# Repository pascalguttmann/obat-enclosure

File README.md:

# Obat - Enclosure

KiCAD Project for the Enclosure adapter PCB to interface to the mechanical Enclosure.

| TOP | BOT |
| ------------- | -------------- |
|  |  |
|  |  |

## License

This repository is licensed under the MIT license.

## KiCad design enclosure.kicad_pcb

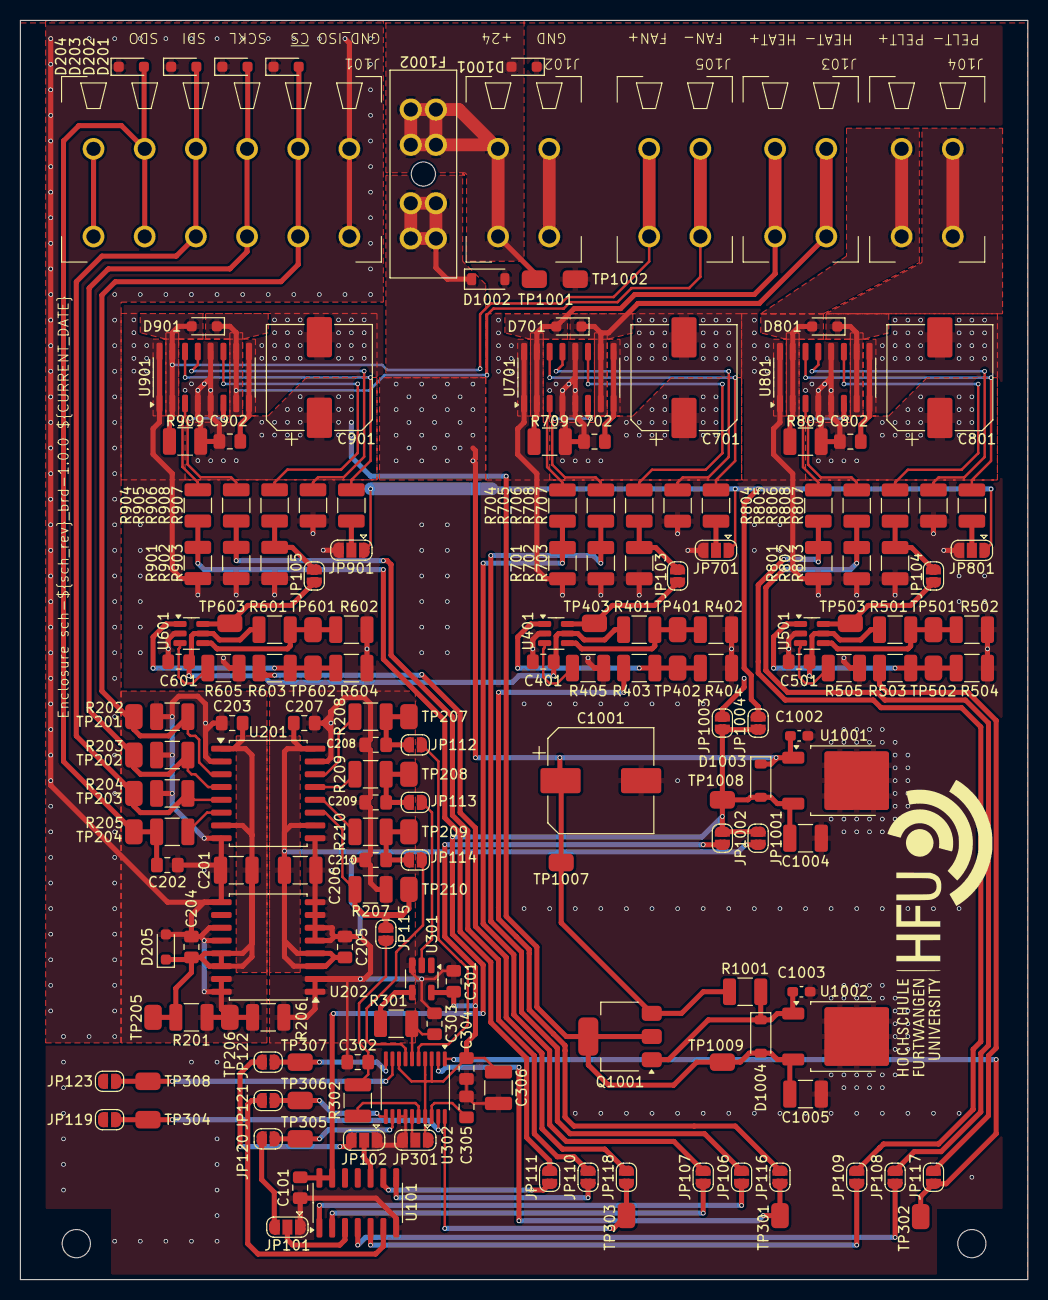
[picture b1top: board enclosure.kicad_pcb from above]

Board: 2 copper layers, 100.0 x 125.0 mm, 181 parts (0 on the bottom side), 100 nets.

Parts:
C101, C203, C204, C205, C207, C301, C304, C305, C401, C501, C601, C702, C802, C902: 100n; C_0805_2012Metric_Pad1.18x1.45mm_HandSolder
C201, C206, C306, C1004, C1005: 10u; C_1210_3225Metric_Pad1.33x2.70mm_HandSolder
C202, C208, C209, C210, C302, C303: 470p; C_0805_2012Metric_Pad1.18x1.45mm_HandSolder
C701, C801, C901, C1001: 470u; CP_Elec_10x10
C1002, C1003: 1u; C_0603_1608Metric_Pad1.08x0.95mm_HandSolder
D201, D202, D203, D204, D701, D801, D901, D1001: D_TVS; D_SOD-323_HandSoldering
D205: PDZ5.6B115; D_SOD-323_HandSoldering
D1002, D1003, D1004: 1N4148; D_SOD-123
F1002: Fuse_Socket; FuseHolder_Blade_ATO_Littelfuse_FLR_178.6165
J101: Conn_01x06_Socket; PhoenixContact_TDPT_2,5_6-SP-5,08_1x06_P5.08mm_Horizontal
J102, J103, J104, J105: Conn_01x02_Socket; PhoenixContact_TDPT_2,5_2-SP-5,08_1x02_P5.08mm_Horizontal
JP101, JP102, JP301, JP701, JP801, JP901: SolderJumper_3_Bridged12; SolderJumper-3_P1.3mm_Bridged12-Soldermask-Paste_RoundedPad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
JP103, JP104, JP105, JP106, JP107, JP108, JP109, JP110, JP111, JP112, JP113, JP114, JP115, JP116, JP117, JP118, JP119, JP120, JP121, JP122, JP123, JP1001, JP1002, JP1003, JP1004: SolderJumper_2_Open; SolderJumper-2_P1.3mm_Open_RoundedPad1.0x1.5mm
Q1001: DPLS350E; SOT-223-3_TabPin2
R201: 330; R_1210_3225Metric_Pad1.30x2.65mm_HandSolder
R202, R203, R204, R206, R207, R401, R501, R601, R701, R702, R703, R801, R802, R803, R901, R902, R903: 1M; R_1210_3225Metric_Pad1.30x2.65mm_HandSolder
R205, R208, R209, R210, R301, R302: 100; R_1210_3225Metric_Pad1.30x2.65mm_HandSolder
R402, R502, R602: 280k; R_1210_3225Metric_Pad1.30x2.65mm_HandSolder
R403, R503, R603, R709, R809, R909: 10k; R_1210_3225Metric_Pad1.30x2.65mm_HandSolder
R404, R504, R604: 2k49; R_1210_3225Metric_Pad1.30x2.65mm_HandSolder
R405, R505, R605: 100k; R_1210_3225Metric_Pad1.30x2.65mm_HandSolder
R704, R705, R706, R707, R708, R804, R805, R806, R807, R808, R904, R905, R906, R907, R908: 1k; R_1210_3225Metric_Pad1.30x2.65mm_HandSolder
R1001: 5R9; R_1210_3225Metric_Pad1.30x2.65mm_HandSolder
TP201, TP202, TP203, TP204, TP205, TP206, TP207, TP208, TP209, TP210, TP301, TP302, TP303, TP304, TP305, TP306, TP307, TP308, TP401, TP402, TP403, TP501, TP502, TP503, TP601, TP602, TP603, TP1001, TP1002, TP1007, TP1008, TP1009: TP_0805_2012Metric
U101: 4041; SOIC-14_3.9x8.7mm_P1.27mm
U201: Si8641BD-B-IS2; SOIC-16W_7.5x10.3mm_P1.27mm
U202: R05C05TE05S; SOIC-16W_7.5x10.3mm_P1.27mm
U301: SN74LVC1G04DBVR; SOT-23-5_HandSoldering
U302: AD567xR; TSSOP-20_4.4x6.5mm_P0.65mm
U401, U501, U601: LTC6992IS6-1; TSOT-23-6
U701, U801, U901: VNH7070ASTR; SO-16_3.9x9.9mm_P1.27mm
U1001: MC7805; TO-252-2
U1002: MC7812; TO-252-2

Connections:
+5VA: C101.2, C1004.2, D1003.2 (A), JP1001.1 (A), JP1002.1 (A), JP1003.1 (A), JP1004.1 (A), TP1008.1, U101.13, U101.14 (Vdd), U1001.3 (OUT)
+5VA_dac: C301.2, C304.2, C306.2, JP301.1 (A), JP1002.2 (B), U301.5 (VCC), U302.3 (VDD), U302.4 (VLOGIC), U302.8 (GAIN), U302.17 (~RESET)
+5VA_digital-interface: C205.2, C206.2, C207.2, JP1001.2 (B), U201.10 (EN2), U201.16 (VDD2), U202.3 (+VIN), U202.4 (+VIN)
+5VA_full-bridge: JP701.1 (A), JP801.1 (A), JP901.1 (A), JP1004.2 (B)
+5VA_pwm: C401.2, C501.2, C601.2, JP1003.2 (B), R401.2, R501.2, R601.2, U401.5 (V+), U501.5 (V+), U601.5 (V+)
+5VI: C201.2, C203.2, C204.2, D205.1 (K), R201.2, TP205.1, U201.1 (VDD1), U201.7 (EN1), U202.13 (+VOUT), U202.14 (+VOUT)
+12VA: C901.1, C902.2, C1005.2, D1004.2 (A), Q1001.2 (C), R909.2, TP1009.1, U901.4 (VCC), U901.5 (VCC), U901.12 (VCC), U1002.3 (OUT)
+24V: C701.1, C702.2, C801.1, C802.2, C1001.1, C1002.2, D1002.1 (K), D1003.1 (K), F1002.1, Q1001.3 (E), R709.2, R809.2, R1001.1, TP1007.1, U701.4 (VCC), U701.5 (VCC), U701.12 (VCC), U801.4 (VCC), U801.5 (VCC), U801.12 (VCC), U1001.1 (IN)
/SCKL: JP113.2 (B), U301.2 (A)
/SDI: JP114.2 (B), U302.7 (SDI)
/SDO: C302.2, JP115.2 (B), R302.1
/dac/dac_ch_0: JP116.1 (A), TP301.1, U302.2 (VOUT0)
/dac/dac_ch_1: JP117.1 (A), TP302.1, U302.1 (VOUT1)
/dac/dac_ch_2: JP118.1 (A), TP303.1, U302.20 (VOUT2)
/dac/dac_ch_3: JP119.1 (A), TP304.1, U302.19 (VOUT3)
/dac/dac_ch_4: JP120.1 (A), TP305.1, U302.12 (VOUT4)
/dac/dac_ch_5: JP121.1 (A), TP306.1, U302.11 (VOUT5)
/dac/dac_ch_6: JP122.1 (A), TP307.1, U302.10 (VOUT6)
/dac/dac_ch_7: JP123.1 (A), TP308.1, U302.9 (VOUT7)
/dac/~sckl: C303.2, R301.2, U302.6 (SCLK)
/dac_ch_0: JP116.2 (B), R403.2
/dac_ch_1: JP117.2 (B), R503.2
/dac_ch_2: JP118.2 (B), R603.2
/dac_ch_4: JP101.3 (B), JP120.2 (B)
/dac_ch_5: JP121.2 (B), U101.6
/dac_ch_6: JP102.3 (B), JP122.2 (B)
/digital-interface/SCKL: C209.2, JP113.1 (A), R209.2, TP208.1
/digital-interface/SCKL_ISO: D202.2 (A2), J101.3, R203.2, TP202.1, U201.4 (A2)
/digital-interface/SDI: C210.2, JP114.1 (A), R210.2, TP209.1
/digital-interface/SDI_ISO: D203.2 (A2), J101.4, R204.2, TP203.1, U201.5 (A3)
/digital-interface/SDO: JP115.1 (A), R207.2, TP210.1, U201.11 (B4)
/digital-interface/SDO_ISO: C202.2, D204.2 (A2), J101.5, R205.1, TP204.1
/digital-interface/sckl_pin: R209.1, U201.13 (B2)
/digital-interface/sdi_pin: R210.1, U201.12 (B3)
/digital-interface/sdo_iso_pin: R205.2, U201.6 (A4)
/digital-interface/~CS_ISO: D201.2 (A2), J101.2, R202.2, TP201.1, U201.3 (A1)
/digital-interface/~CS: C208.2, JP112.1 (A), R208.2, TP207.1
/digital-interface/~cs_pin: R208.1, U201.14 (B1)
/fan_+: D901.2 (A2), J105.2, R909.1, U901.2 (OUT_A), U901.15 (OUT_A)
/fan_-: D901.1 (A1), J105.1, U901.7 (OUT_B), U901.10 (OUT_B)
/full-bridge1/IN_A: JP109.2 (B), R801.2, R804.1
/full-bridge1/IN_B: JP108.2 (B), R802.2, R805.1
/full-bridge1/cs: R808.2, U801.13 (CS)
/full-bridge1/in_a: R804.2, U801.3 (IN_A)
/full-bridge1/in_b: R805.2, U801.6 (IN_B)
/full-bridge1/pwm: R806.2, U801.11 (PWM)
/full-bridge1/sel0: R807.2, U801.14 (SEL0)
/full-bridge1/sel0_in: JP801.2 (C), R807.1
/full-bridge2/IN_A: JP111.2 (B), R901.2, R904.1
/full-bridge2/IN_B: JP110.2 (B), R902.2, R905.1
/full-bridge2/cs: R908.2, U901.13 (CS)
/full-bridge2/in_a: R904.2, U901.3 (IN_A)
/full-bridge2/in_b: R905.2, U901.6 (IN_B)
/full-bridge2/pwm: R906.2, U901.11 (PWM)
/full-bridge2/sel0: R907.2, U901.14 (SEL0)
/full-bridge2/sel0_in: JP901.2 (C), R907.1
/full-bridge/IN_A: JP107.2 (B), R701.2, R704.1
/full-bridge/IN_B: JP106.2 (B), R702.2, R705.1
/full-bridge/cs: R708.2, U701.13 (CS)
/full-bridge/in_a: R704.2, U701.3 (IN_A)
/full-bridge/in_b: R705.2, U701.6 (IN_B)
/full-bridge/pwm: R706.2, U701.11 (PWM)
/full-bridge/sel0: R707.2, U701.14 (SEL0)
/full-bridge/sel0_in: JP701.2 (C), R707.1
/heater_+: D701.2 (A2), J103.2, R709.1, U701.2 (OUT_A), U701.15 (OUT_A)
/heater_-: D701.1 (A1), J103.1, U701.7 (OUT_B), U701.10 (OUT_B)
/peltier_+: D801.2 (A2), J104.2, R809.1, U801.2 (OUT_A), U801.15 (OUT_A)
/peltier_-: D801.1 (A1), J104.1, U801.7 (OUT_B), U801.10 (OUT_B)
/power/IN: D1001.2 (A2), F1002.2, J102.2, TP1001.1
/pwm1/div: R501.1, R502.2, TP501.1, U501.4 (DIV)
/pwm1/mod_pin: R503.1, R504.2, TP502.1, U501.1 (MOD)
/pwm1/pwm: JP104.1 (A), TP503.1, U501.6 (OUT)
/pwm1/set: R505.2, U501.3 (SET)
/pwm2/div: R601.1, R602.2, TP601.1, U601.4 (DIV)
/pwm2/mod_pin: R603.1, R604.2, TP602.1, U601.1 (MOD)
/pwm2/pwm: JP105.1 (A), TP603.1, U601.6 (OUT)
/pwm2/set: R605.2, U601.3 (SET)
/pwm/div: R401.1, R402.2, TP401.1, U401.4 (DIV)
/pwm/mod_pin: R403.1, R404.2, TP402.1, U401.1 (MOD)
/pwm/pwm: JP103.1 (A), TP403.1, U401.6 (OUT)
/pwm/set: R405.2, U401.3 (SET)
/pwm_fan: JP105.2 (B), R903.2, R906.1
/pwm_heater: JP103.2 (B), R703.2, R706.1
/pwm_peltier: JP104.2 (B), R803.2, R806.1
/~CS: JP112.2 (B), U302.5 (~SYNC)
GND: C101.1, C205.1, C206.1, C207.1, C208.1, C209.1, C210.1, C301.1, C302.1, C303.1, C304.1, C305.2, C306.1, C401.1, C501.1, C601.1, C701.2, C702.1, C801.2, C802.1, C901.2, C902.1, C1001.2, C1002.1, C1003.1, C1004.1, C1005.1, D1001.1 (A1), D1002.2 (A), J102.1, JP101.1 (A), JP102.1 (A), JP301.3 (B), JP701.3 (B), JP801.3 (B), JP901.3 (B), R206.2, R207.1, R402.1, R404.1, R405.1, R502.1, R504.1, R505.1, R602.1, R604.1, R605.1, R701.1, R702.1, R703.1, R708.1, R801.1, R802.1, R803.1, R808.1, R901.1, R902.1, R903.1, R908.1, TP1002.1, U101.7 (Vss), U201.9 (GND2), U201.15 (GND2), U202.1 (-VIN), U202.2 (-VIN), U202.5 (SGND_IN), U202.6 (SGND_IN), U202.7 (SGND_IN), U202.8 (SGND_IN), U301.3 (GND), U302.13 (GND), U302.14 (RSTSEL), U401.2 (GND), U501.2 (GND), U601.2 (GND), U701.1 (GND_A), U701.8 (GND_B), U701.9 (GND_B), U701.16 (GND_A), U801.1 (GND_A), U801.8 (GND_B), U801.9 (GND_B), U801.16 (GND_A), U901.1 (GND_A), U901.8 (GND_B), U901.9 (GND_B), U901.16 (GND_A), U1001.2 (GND), U1002.2 (GND)
GNDI: C201.1, C202.1, C203.1, C204.1, D201.1 (A1), D202.1 (A1), D203.1 (A1), D204.1 (A1), D205.2 (A), J101.1, R201.1, R202.1, R203.1, R204.1, R206.1, TP206.1, U201.2 (GND1), U201.8 (GND1), U202.9 (SGND_OUT), U202.11 (SGND_OUT), U202.12 (SGND_OUT), U202.15 (-VOUT), U202.16 (-VOUT)
unnamed: C1003.2, D1004.1 (K), Q1001.1 (B), R1001.2, U1002.1 (IN)
unnamed: JP101.2 (C), U101.3
unnamed: JP102.2 (C), U101.10
unnamed: JP106.1 (A), U101.1
unnamed: JP107.1 (A), U101.2
unnamed: JP108.1 (A), U101.4
unnamed: JP109.1 (A), U101.5
unnamed: JP110.1 (A), U101.8
unnamed: JP111.1 (A), U101.9
unnamed: JP301.2 (C), U302.15 (~LDAC)
unnamed: R301.1, U301.4 (Y)
unnamed: R302.2, U302.16 (SDO)
unnamed: C305.1, U302.18 (VREF)

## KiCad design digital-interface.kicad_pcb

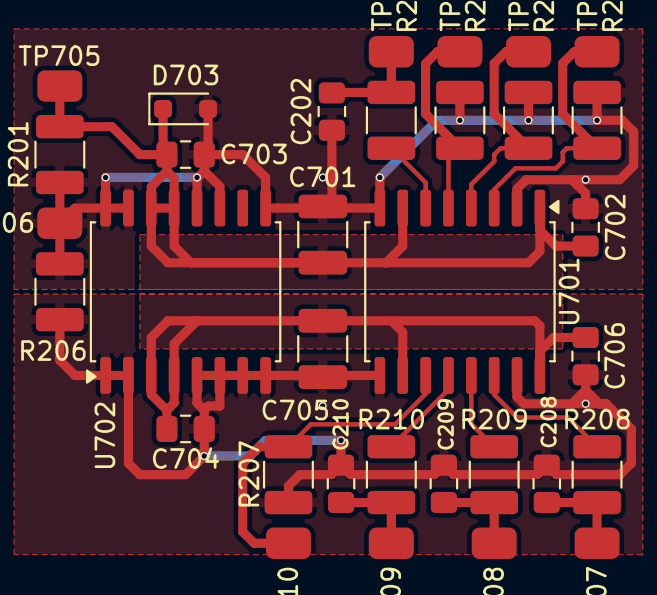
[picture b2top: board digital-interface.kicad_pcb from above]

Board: 2 copper layers, 33 parts (0 on the bottom side), 16 nets.

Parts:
C202, C208, C209, C210: 470p; C_0805_2012Metric_Pad1.18x1.45mm_HandSolder
C701, C705: 10u; C_1210_3225Metric_Pad1.33x2.70mm_HandSolder
C702, C703, C704, C706: 100n; C_0805_2012Metric_Pad1.18x1.45mm_HandSolder
D703: PDZ5.6B115; D_SOD-323_HandSoldering
R201: 330; R_1210_3225Metric_Pad1.30x2.65mm_HandSolder
R202, R203, R204, R206, R207: 1M; R_1210_3225Metric_Pad1.30x2.65mm_HandSolder
R205, R208, R209, R210: 100; R_1210_3225Metric_Pad1.30x2.65mm_HandSolder
TP701, TP702, TP703, TP704, TP705, TP706, TP707, TP708, TP709, TP710: TP_0805_2012Metric
U701: Si8641BD-B-IS2; SOIC-16W_7.5x10.3mm_P1.27mm
U702: R05C05TE05S; SOIC-16W_7.5x10.3mm_P1.27mm

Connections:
+5VA_digital-interface: C704.2, C705.2, C706.2, U701.10 (EN2), U701.16 (VDD2), U702.3 (+VIN), U702.4 (+VIN)
+5VI: C701.2, C702.2, C703.2, D703.1 (K), R201.2, TP705.1, U701.1 (VDD1), U701.7 (EN1), U702.13 (+VOUT), U702.14 (+VOUT)
/SCKL: C209.2, R209.2, TP708.1
/SCKL_ISO: R203.2, TP702.1, U701.4 (A2)
/SDI: C210.2, R210.2, TP709.1
/SDI_ISO: R204.2, TP703.1, U701.5 (A3)
/SDO: R207.2, TP710.1, U701.11 (B4)
/SDO_ISO: C202.2, R205.1, TP704.1
/sckl_pin: R209.1, U701.13 (B2)
/sdi_pin: R210.1, U701.12 (B3)
/sdo_iso_pin: R205.2, U701.6 (A4)
/~CS_ISO: R202.2, TP701.1, U701.3 (A1)
/~CS: C208.2, R208.2, TP707.1
/~cs_pin: R208.1, U701.14 (B1)
GND: C208.1, C209.1, C210.1, C704.1, C705.1, C706.1, R206.2, R207.1, U701.9 (GND2), U701.15 (GND2), U702.1 (-VIN), U702.2 (-VIN), U702.5 (SGND_IN), U702.6 (SGND_IN), U702.7 (SGND_IN), U702.8 (SGND_IN)
GNDI: C202.1, C701.1, C702.1, C703.1, D703.2 (A), R201.1, R202.1, R203.1, R204.1, R206.1, TP706.1, U701.2 (GND1), U701.8 (GND1), U702.9 (SGND_OUT), U702.11 (SGND_OUT), U702.12 (SGND_OUT), U702.15 (-VOUT), U702.16 (-VOUT)

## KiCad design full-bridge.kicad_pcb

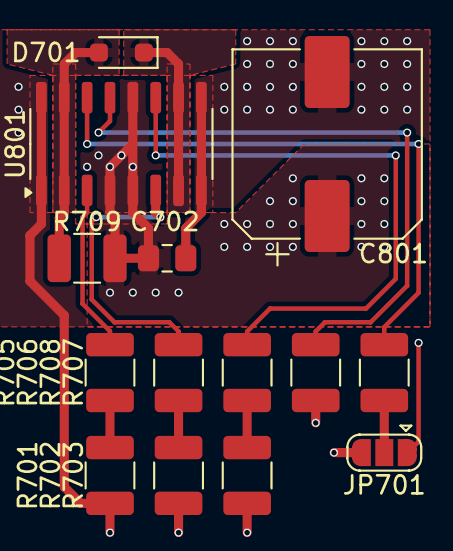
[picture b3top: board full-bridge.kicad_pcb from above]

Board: 2 copper layers, 14 parts (0 on the bottom side), 13 nets.

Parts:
C702: 100n; C_0805_2012Metric_Pad1.18x1.45mm_HandSolder
C801: 470u; CP_Elec_10x10
D701: D_TVS; D_SOD-323_HandSoldering
JP701: SolderJumper_3_Bridged12; SolderJumper-3_P1.3mm_Bridged12-Soldermask-Paste_RoundedPad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
R701, R702, R703: 1M; R_1210_3225Metric_Pad1.30x2.65mm_HandSolder
R704, R705, R706, R707, R708: 1k; R_1210_3225Metric_Pad1.30x2.65mm_HandSolder
R709: 10k; R_1210_3225Metric_Pad1.30x2.65mm_HandSolder
U801: VNH7070ASTR; SO-16_3.9x9.9mm_P1.27mm

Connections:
/IN_A: R701.2, R704.1
/IN_B: R702.2, R705.1
/OUT_A: D701.2 (A2), R709.1, U801.2 (OUT_A), U801.15 (OUT_A)
/OUT_B: D701.1 (A1), U801.7 (OUT_B), U801.10 (OUT_B)
/PWM: R703.2, R706.1
/VCC: C702.2, C801.1, R709.2, U801.4 (VCC), U801.5 (VCC), U801.12 (VCC)
/cs: R708.2, U801.13 (CS)
/in_a: R704.2, U801.3 (IN_A)
/in_b: R705.2, U801.6 (IN_B)
/pwm: R706.2, U801.11 (PWM)
/sel0: R707.2, U801.14 (SEL0)
/sel0_in: JP701.2 (C), R707.1
GND: C702.1, C801.2, JP701.3 (B), R701.1, R702.1, R703.1, R708.1, U801.1 (GND_A), U801.8 (GND_B), U801.9 (GND_B), U801.16 (GND_A)

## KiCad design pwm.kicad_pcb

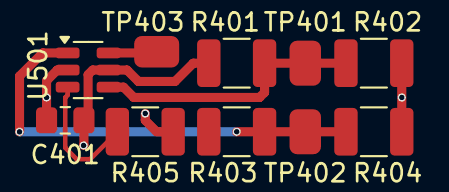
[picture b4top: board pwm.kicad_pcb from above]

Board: 2 copper layers, 10 parts (0 on the bottom side), 6 nets.

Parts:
C401: 100n; C_0805_2012Metric_Pad1.18x1.45mm_HandSolder
R401: 1M; R_1210_3225Metric_Pad1.30x2.65mm_HandSolder
R402: 280k; R_1210_3225Metric_Pad1.30x2.65mm_HandSolder
R403: 10k; R_1210_3225Metric_Pad1.30x2.65mm_HandSolder
R404: 2k49; R_1210_3225Metric_Pad1.30x2.65mm_HandSolder
R405: 100k; R_1210_3225Metric_Pad1.30x2.65mm_HandSolder
TP401, TP402, TP403: TP_0805_2012Metric
U501: LTC6992IS6-1; TSOT-23-6

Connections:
+5VA_pwm: C401.2, R401.2, U501.5 (V+)
/div: R401.1, R402.2, TP401.1, U501.4 (DIV)
/mod_pin: R403.1, R404.2, TP402.1, U501.1 (MOD)
/pwm: TP403.1, U501.6 (OUT)
/set: R405.2, U501.3 (SET)
GND: C401.1, R402.1, R404.1, R405.1, U501.2 (GND)

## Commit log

2025-02-19 add README
2025-02-19 add MIT license
2025-02-19 add .gitignore for KiCad Project
2025-02-19 create kicad project and kicad schematic
2025-02-19 import schematic settings from pss
2025-02-19 add enclosure symbol library
2025-02-19 import relevant symbols from pss
2025-02-20 add digital-interface from pss
2025-02-20 edit digital-interface rise time limitation with lowpass filter
2025-02-20 edit enclosure digital-interface increase minimal load current to 15mA
2025-02-20 edit enclosure digital-interface add esd protection resistor
2025-02-20 reannotate enclosure digital-interface
2025-02-20 add enclosure integration of digital-interface in overview
2025-02-20 fix enclosure digital-interface stray wire in schmematic
2025-02-20 fix enclosure digital-interface esd protection resistor shall be 1MR not 1kR
2025-02-20 add enclosure digital-interface pull down resistors at inputs
2025-02-20 export schematic version 0.1.0
2025-02-20 add enclosure dac sub circuit
2025-02-20 add enclosure pwm sub circuit
2025-02-20 add enclosure full-bridge sub circuit
2025-02-20 add enclosure power sub circuit
2025-02-20 add enclosure output connectors
2025-02-21 add increased current capacity for 12V power rail
2025-02-21 fix symbol library link
2025-02-21 update datasheets and footprint references
2025-02-21 add enclosure kicad_pcb
2025-02-21 add full-bridge sub layout
2025-02-21 add pwm sub layout
2025-02-21 ajust output channel order
2025-02-21 add digital-interface sub layout
2025-02-21 fix zone nets
2025-02-21 fix netnaming collsion
2025-02-21 add power sub-layout
2025-02-22 add dac sub-layout
2025-02-22 adapt pcb size to 100x125 mm^2
2025-02-22 enhance zone edges
2025-02-22 enhance silk screen
2025-02-22 fix erc errors
2025-02-22 fix drc errors
2025-02-22 add gerber export
2025-02-22 add ibom
2025-02-23 add 3d model images
2025-03-06 fix wrong fuse in bom
